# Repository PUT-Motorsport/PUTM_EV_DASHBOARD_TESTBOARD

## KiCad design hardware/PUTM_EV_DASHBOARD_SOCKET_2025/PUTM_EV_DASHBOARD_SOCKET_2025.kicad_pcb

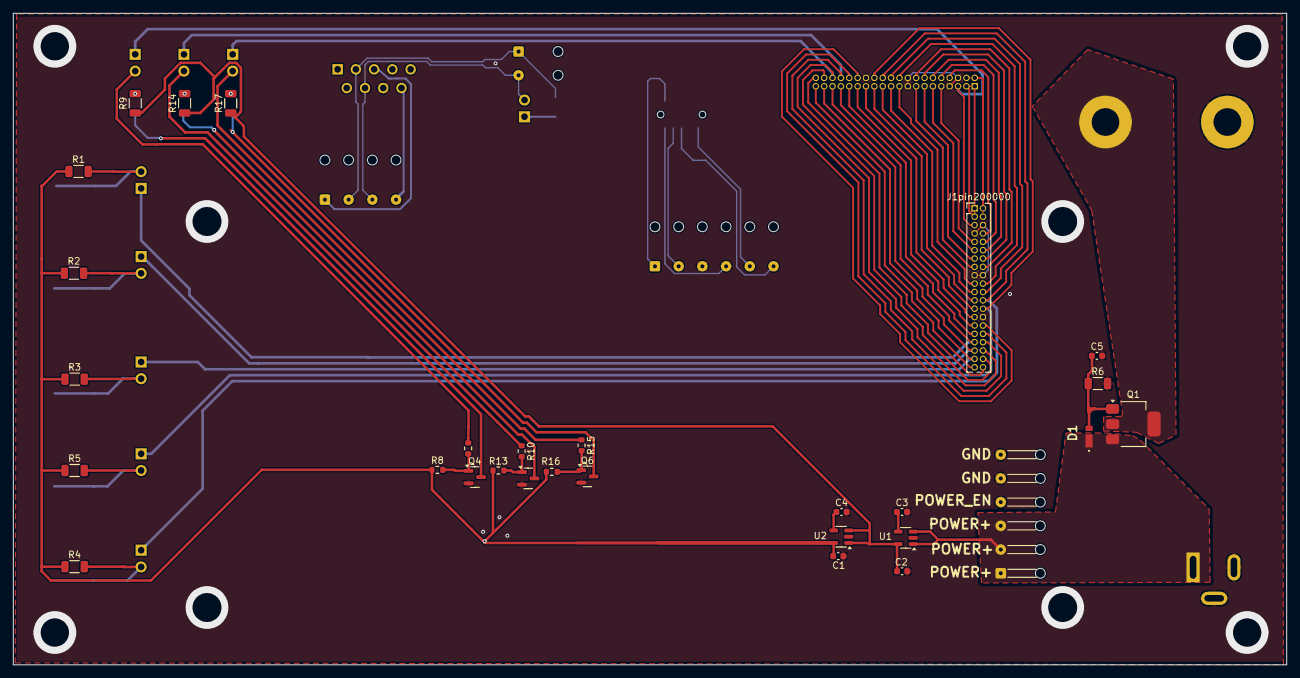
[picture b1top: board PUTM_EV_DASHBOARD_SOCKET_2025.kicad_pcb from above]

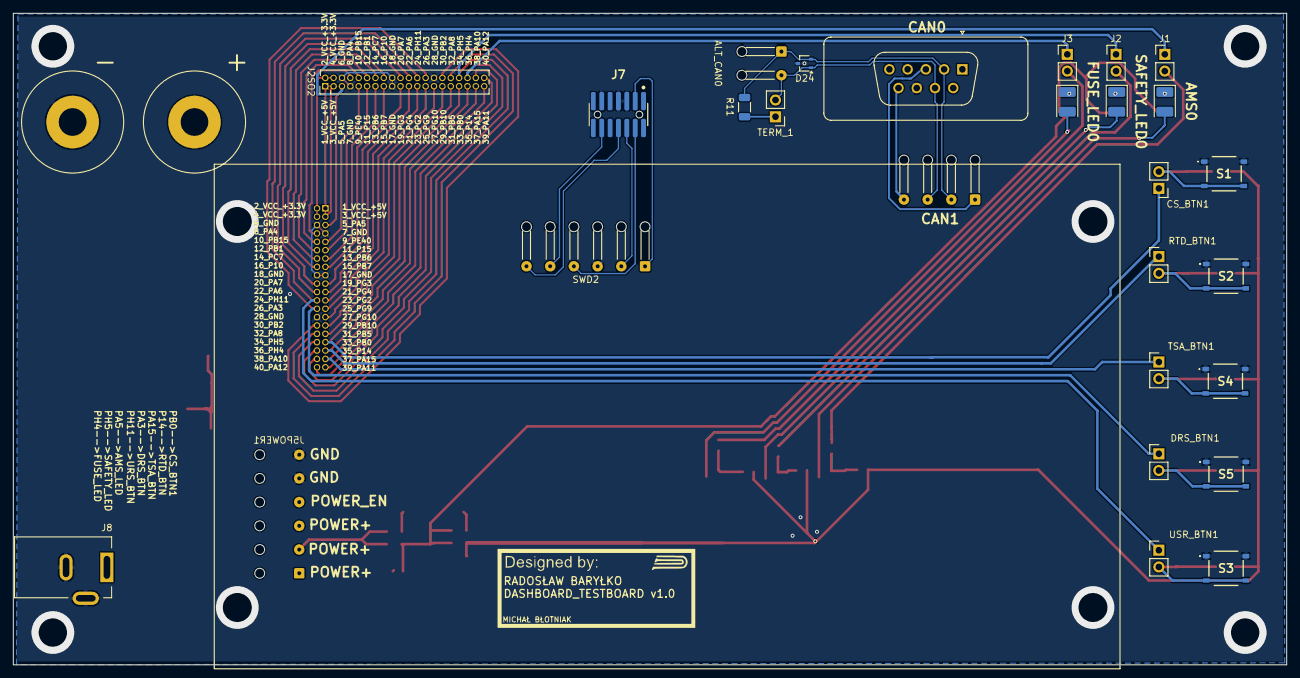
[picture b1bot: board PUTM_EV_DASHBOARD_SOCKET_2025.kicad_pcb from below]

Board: 2 copper layers, 193.3 x 98.9 mm, 57 parts (28 on the bottom side), 68 nets.

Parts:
ALT_CAN0: Conn_01x02_Pin; SolderWire-0.1sqmm_1x02_P3.6mm_D0.4mm_OD1mm_Relief
AMS0: Yellow; LED_PLCC-2_3.4x3.0mm_AK
C1, C2: 2u; C_0603_1608Metric
C3, C4: 10n; C_0603_1608Metric
C5: 22n; C_0603_1608Metric
CAN0: Conn_01x09; DSUB-9_Socket_Vertical_P2.77x2.84mm
CAN1: Conn_01x04_MountingPin; SolderWire-0.1sqmm_1x04_P3.6mm_D0.4mm_OD1mm_Relief
CS_BTN1: Conn_01x02_Pin; PinHeader_1x02_P2.54mm_Vertical
D1: TDZVTR12; TDZVTR20
D24: PESD2IVN24-U; SOT-323_SC-70
DRS_BTN1: Conn_01x02_Pin; PinHeader_1x02_P2.54mm_Vertical
FUSE_LED0: Yellow; LED_PLCC-2_3.4x3.0mm_AK
J1, J2, J3: Conn_01x02_Pin; PinHeader_1x02_P2.54mm_Vertical
J1pin200000, J2SO2: Conn_02x20_Top_Bottom_MountingPin; PinHeader_2x20_P1.27mm_Vertical
J4, J5: Conn_01x01; D-3230
J5POWER1: Conn_01x06_MountingPin; SolderWire-0.1sqmm_1x06_P3.6mm_D0.4mm_OD1mm_Relief
J7: FTSH; FTSH-107-XX-YYY-DV-K-A
J8: Conn_01x03_Socket; BarrelJack_Kycon_KLDX-0202-xC_Horizontal
Q1: STN3P6F6; SOT-223-3_TabPin2
Q4, Q5, Q6: BSS138; SOT-23
R1, R2, R3, R4, R5: 1K; R_1206_3216Metric
R6, R9, R14, R17: 150; R_1206_3216Metric
R7, R10, R15: 100R; R_0603_1608Metric
R8, R13, R16: 10k; R_0603_1608Metric
R11: 120; R_1206_3216Metric
RTD_BTN1: Conn_01x02_Pin; PinHeader_1x02_P2.54mm_Vertical
S1, S2, S3, S4, S5: PTS526SM15SMTR2_LFS; PTS526SM15SMTR2LFS
SAFETY_LED0: Yellow; LED_PLCC-2_3.4x3.0mm_AK
SWD2: Conn_01x06_MountingPin; SolderWire-0.1sqmm_1x06_P3.6mm_D0.4mm_OD1mm_Relief
TERM_1: Conn_01x02_Pin; PinHeader_1x02_P2.54mm_Vertical
TSA_BTN1: Conn_01x02_Pin; PinHeader_1x02_P2.54mm_Vertical
U1: SPX3819M5-L-5-0; SOT-23-5
U2: SPX3819M5-L-3-3; SOT-23-5
USR_BTN1: Conn_01x02_Pin; PinHeader_1x02_P2.54mm_Vertical

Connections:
+3.3V: C1.1, R1.1, R2.1, R3.1, R4.1, R5.1, R8.1, R13.1, R16.1, U2.5 (OUT)
+5V: C2.1, R9.1, R14.1, R17.1, U1.5 (OUT), U2.1 (IN), U2.3 (EN)
/BUTTON_1: CS_BTN1.2, R1.2, S1.3 (NO_1), S1.4 (NO_2)
/BUTTON_2: R2.2, RTD_BTN1.2, S2.3 (NO_1), S2.4 (NO_2)
/BUTTON_3: R3.2, S4.3 (NO_1), S4.4 (NO_2), TSA_BTN1.2
/BUTTON_4: R4.2, S3.3 (NO_1), S3.4 (NO_2), USR_BTN1.2
/BUTTON_5: DRS_BTN1.2, R5.2, S5.3 (NO_1), S5.4 (NO_2)
/CAN/CAN_GND: CAN0.3, CAN1.1
/CAN/CAN_N: ALT_CAN0.1, CAN0.2, CAN1.2, D24.2 (A2), R11.1
/CAN/CAN_P: ALT_CAN0.2, CAN0.7, CAN1.3, D24.1 (A1), TERM_1.2
/CAN/CAN_VDD: CAN0.9, CAN1.4
/LED_1: J1.2, R7.1
/LED_2: J3.2, R15.1
/LED_3: J2.2, R10.1
/POWER/BANANA_JACK: J4.1, Q1.2 (D)
/POWER/POWER1: D1.1 (K), J5POWER1.1, J5POWER1.2, J5POWER1.3, J8.1, Q1.3 (S), U1.1 (IN), U1.3 (EN)
/SOCKETS_2X20/<NO NET>: J1pin200000.1, J1pin200000.3, J2SO2.1, J2SO2.3
/SOCKETS_2X20/P10: J1pin200000.16, J2SO2.16
/SOCKETS_2X20/P14: J1pin200000.35, J2SO2.35, RTD_BTN1.1
/SOCKETS_2X20/P15: J1pin200000.11, J2SO2.11
/SOCKETS_2X20/PA3: DRS_BTN1.1, J1pin200000.26, J2SO2.26
/SOCKETS_2X20/PA4: J1pin200000.8, J2SO2.8
/SOCKETS_2X20/PA5: J1.1, J1pin200000.5, J2SO2.5
/SOCKETS_2X20/PA6: J1pin200000.22, J2SO2.22
/SOCKETS_2X20/PA7: J1pin200000.20, J2SO2.20
/SOCKETS_2X20/PA8: J1pin200000.32, J2SO2.32
/SOCKETS_2X20/PA10: J1pin200000.38, J2SO2.38
/SOCKETS_2X20/PA11: J1pin200000.39, J2SO2.39
/SOCKETS_2X20/PA12: J1pin200000.40, J2SO2.40
/SOCKETS_2X20/PA15: J1pin200000.37, J2SO2.37, TSA_BTN1.1
/SOCKETS_2X20/PB0: CS_BTN1.1, J1pin200000.33, J2SO2.33
/SOCKETS_2X20/PB1: J1pin200000.12, J2SO2.12
/SOCKETS_2X20/PB2: J1pin200000.30, J2SO2.30
/SOCKETS_2X20/PB5: J1pin200000.31, J2SO2.31
/SOCKETS_2X20/PB6: J1pin200000.13, J2SO2.13
/SOCKETS_2X20/PB7: J1pin200000.15, J2SO2.15
/SOCKETS_2X20/PB10: J1pin200000.29, J2SO2.29
/SOCKETS_2X20/PB15: J1pin200000.10, J2SO2.10
/SOCKETS_2X20/PC7: J1pin200000.14, J2SO2.14
/SOCKETS_2X20/PE40: J1pin200000.9, J2SO2.9
/SOCKETS_2X20/PG2: J1pin200000.23, J2SO2.23
/SOCKETS_2X20/PG3: J1pin200000.19, J2SO2.19
/SOCKETS_2X20/PG4: J1pin200000.21, J2SO2.21
/SOCKETS_2X20/PG9: J1pin200000.25, J2SO2.25
/SOCKETS_2X20/PG10: J1pin200000.27, J2SO2.27
/SOCKETS_2X20/PH4: J1pin200000.36, J2SO2.36, J3.1
/SOCKETS_2X20/PH5: J1pin200000.34, J2.1, J2SO2.34
/SOCKETS_2X20/PH11: J1pin200000.24, J2SO2.24, USR_BTN1.1
/SOCKETS_2X20/VCC: J1pin200000.2, J1pin200000.4, J2SO2.2, J2SO2.4
/SWD/SWD_RST: J7.12, SWD2.5
/SWD/SWD_SWO: J7.8, SWD2.6
/SWD/SWD_SW_CLK: J7.6, SWD2.2
/SWD/SWD_SW_DIO: J7.4, SWD2.4
/SWD/SWD_VCC_+3.3V: J7.3, SWD2.1
GND: C1.2, C2.2, C3.2, C4.2, C5.2, CAN0.8, D24.3 (common), J1pin200000.6, J1pin200000.7, J1pin200000.17, J1pin200000.18, J1pin200000.28, J2SO2.6, J2SO2.7, J2SO2.17, J2SO2.18, J2SO2.28, J5.1, J5POWER1.5, J5POWER1.6, J7.5, J7.7, J7.11, J8.2, J8.3, Q4.2 (S), Q5.2 (S), Q6.2 (S), R6.2, S1.1 (COM_1), S1.2 (COM_2), S2.1 (COM_1), S2.2 (COM_2), S3.1 (COM_1), S3.2 (COM_2), S4.1 (COM_1), S4.2 (COM_2), S5.1 (COM_1), S5.2 (COM_2), SWD2.3, U1.2 (GND), U2.2 (GND)
unnamed: AMS0.2 (A), R9.2
unnamed: AMS0.1 (K), Q4.3 (D)
unnamed: C5.1, D1.2 (A), Q1.1 (G), R6.1
unnamed: FUSE_LED0.2 (A), R17.2
unnamed: FUSE_LED0.1 (K), Q6.3 (D)
unnamed: Q4.1 (G), R7.2, R8.2
unnamed: Q5.3 (D), SAFETY_LED0.1 (K)
unnamed: Q5.1 (G), R10.2, R13.2
unnamed: Q6.1 (G), R15.2, R16.2
unnamed: R14.2, SAFETY_LED0.2 (A)
unnamed: R11.2, TERM_1.1
unnamed: C3.1, U1.4 (BP)
unnamed: C4.1, U2.4 (BP)

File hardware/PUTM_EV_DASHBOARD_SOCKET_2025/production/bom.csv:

Designator,Footprint,Quantity,Value,LCSC Part #
ALT_CAN0,SolderWire-0.1sqmm_1x02_P3.6mm_D0.4mm_OD1mm_Relief,1,Conn_01x02_Pin,
"AMS0, FUSE_LED0, SAFETY_LED0",LED_PLCC-2_3.4x3.0mm_AK,3,Yellow,
"C1, C2",0603,2,2u,
"C3, C4",0603,2,10n,
C5,0603,1,22n,
CAN0,DSUB-9_Socket_Vertical_P2.77x2.84mm,1,Conn_01x09,
CAN1,SolderWire-0.1sqmm_1x04_P3.6mm_D0.4mm_OD1mm_Relief,1,Conn_01x04_MountingPin,
"CS_BTN1, DRS_BTN1, J1, J2, J3, RTD_BTN1, TERM_1, TSA_BTN1, USR_BTN1",PinHeader_1x02_P2.54mm_Vertical,9,Conn_01x02_Pin,
D1,TDZVTR20,1,TDZVTR12,
D24,SOT-323_SC-70,1,PESD2IVN24-U,
"J1PIN200000, J2SO2",PinHeader_2x20_P1.27mm_Vertical,2,Conn_02x20_Top_Bottom_MountingPin,
"J4, J5",D-3230,2,Conn_01x01,
"J5POWER1, SWD2",SolderWire-0.1sqmm_1x06_P3.6mm_D0.4mm_OD1mm_Relief,2,Conn_01x06_MountingPin,
J7,FTSH-107-XX-YYY-DV-K-A,1,FTSH,
J8,BarrelJack_Kycon_KLDX-0202-xC_Horizontal,1,Conn_01x03_Socket,
Q1,SOT-223-3_TabPin2,1,STN3P6F6,
"Q4, Q5, Q6",SOT-23,3,BSS138,
"R1, R2, R3, R4, R5",1206,5,1K,
"R10, R15, R7",0603,3,100R,
R11,1206,1,120,
"R13, R16, R8",0603,3,10k,
"R14, R17, R6, R9",1206,4,150,
"S1, S2, S3, S4, S5",PTS526SM15SMTR2LFS,5,PTS526SM15SMTR2_LFS,
U1,SOT-23-5,1,SPX3819M5-L-5-0,
U2,SOT-23-5,1,SPX3819M5-L-3-3,

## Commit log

2025-10-07 prawie gotowe
2025-10-07 gotowe
2025-10-13 jest jako tako
2025-10-13 jest lepiej
2025-10-14 jest
2025-10-18 poprawione opisy i złącze swd
2025-10-19 poprawione opisy i złącze swd, gnazdo POWER jest na krawędzi płytki
2025-10-19 poprawione opisy i złącze swd, gnazdo POWER jest na krawędzi płytki.
2025-10-24 dodano łezki do pól smd, pola lutownicze do przelotek, dodano zabezpieczenie przed odwrotna polaryzacją, odsunięto ścieżki od krawędzi płytki, poprawiono can,
2025-10-25 Cosmetic corrections
2025-10-25 sync
2025-10-25 Bogracz Czas przygotowania: 3 godziny 30 minut Liczba porcji: 2100 g gulaszu W 100 g dania: Wartość energetyczna 156 kcal Węglowodany 5 g - W tym cukry 2 g Białko 7 g Tłuszcze 12 g
    Składniki
    800 g mięsa wołowego - np. pręga oraz łopatka
    200 g boczku gotowanego wędzonego
    100 g dobrej jakosci słoniny
    6 łyżek dobrej jakości smalcu - około 100 g
    2 średniej wielkości cebule - około 330 g
2026-01-02 added production files
2026-03-07 fixed button logic, holes for inserts, distance from mounting holes to P4 socket, changed jumpers, TVS diode and footprint for laboratory socket 4m
2026-03-17 fixed layout
2026-03-19 fixed button text layout
2026-03-19 ready to production v1.1
2026-03-19 ready to production
